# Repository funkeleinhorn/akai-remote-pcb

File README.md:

<!--
SPDX-FileCopyrightText: 2025 Funkeleinhorn <git@funkeleinhorn.com>
SPDX-License-Identifier: GPL-3.0-or-later
-->

# Keymatrix

A PCB which fits in the remote control port of AKAI GX 635s featuring an ESP32 to allow remote control.
This project is licensed as open hardware. See LICENSE.txt for details.

## Images

Here you can see how the PCB looks:

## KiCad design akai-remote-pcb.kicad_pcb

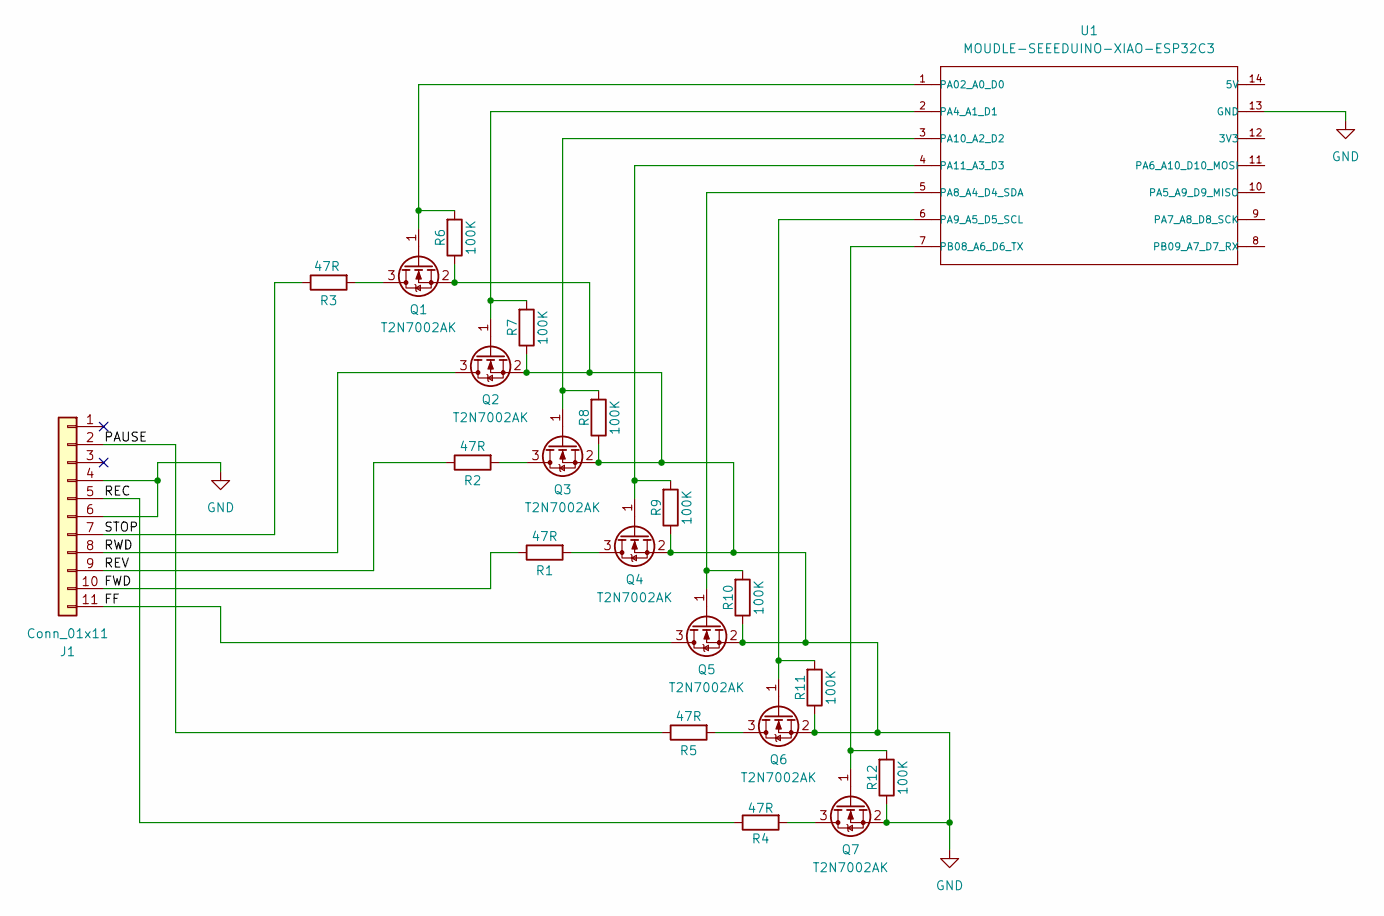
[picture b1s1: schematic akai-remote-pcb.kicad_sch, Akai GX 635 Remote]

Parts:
J1: Conn_01x11; AKAI_GX_635_REMOTE_CONTROL_PORT
Q1, Q2, Q3, Q4, Q5, Q6, Q7: T2N7002AK; SOT-23
R1, R2, R3, R4, R5: 47R; R_0603_1608Metric
R6, R7, R8, R9, R10, R11, R12: 100K; R_0603_1608Metric
U1: MOUDLE-SEEEDUINO-XIAO-ESP32C3; MOUDLE14P-SMD-2.54-21X17.8MM

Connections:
/FF: J1.11, Q5.3 (D)
/FWD: J1.10, R1.1
/PAUSE: J1.2, R5.1
/REC: J1.5, R4.1
/REV: J1.9, R2.1
/RWD: J1.8, Q2.3 (D)
/STOP: J1.7, R3.1
GND: J1.4, J1.6, Q1.2 (S), Q2.2 (S), Q3.2 (S), Q4.2 (S), Q5.2 (S), Q6.2 (S), Q7.2 (S), R6.1, R7.1, R8.1, R9.1, R10.1, R11.1, R12.1, U1.13 (GND)
unnamed: Q1.3 (D), R3.2
unnamed: Q1.1 (G), R6.2, U1.1 (PA02_A0_D0)
unnamed: Q2.1 (G), R7.2, U1.2 (PA4_A1_D1)
unnamed: Q3.3 (D), R2.2
unnamed: Q3.1 (G), R8.2, U1.3 (PA10_A2_D2)
unnamed: Q4.3 (D), R1.2
unnamed: Q4.1 (G), R9.2, U1.4 (PA11_A3_D3)
unnamed: Q5.1 (G), R10.2, U1.5 (PA8_A4_D4_SDA)
unnamed: Q6.3 (D), R5.2
unnamed: Q6.1 (G), R11.2, U1.6 (PA9_A5_D5_SCL)
unnamed: Q7.3 (D), R4.2
unnamed: Q7.1 (G), R12.2, U1.7 (PB08_A6_D6_TX)

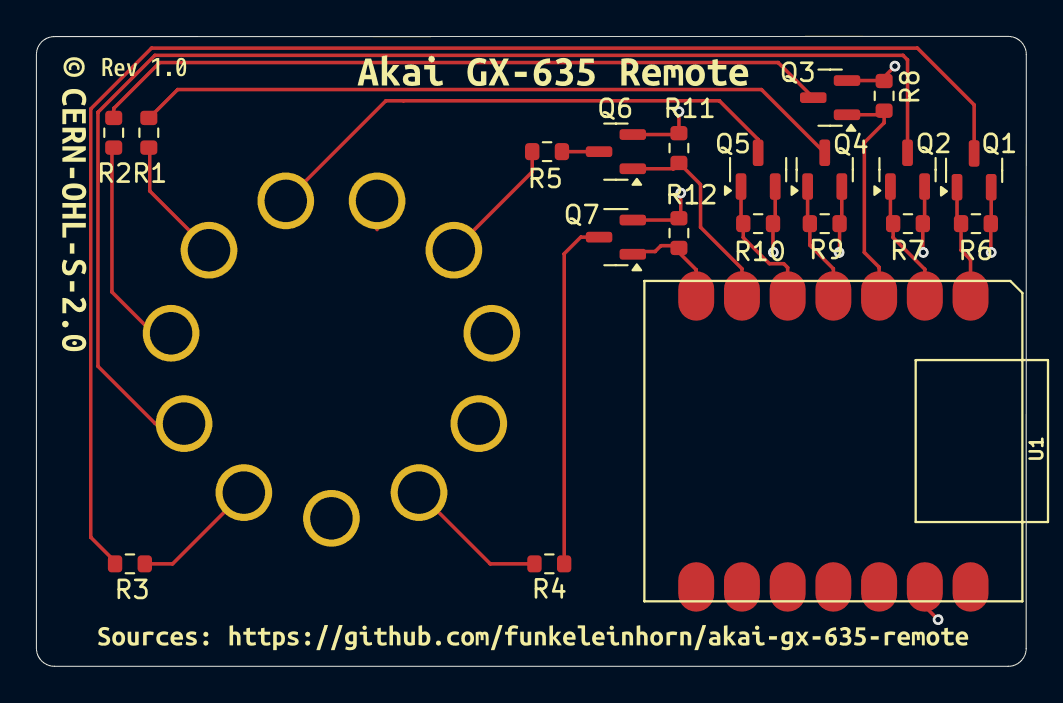
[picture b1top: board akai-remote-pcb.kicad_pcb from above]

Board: 2 copper layers, 55.0 x 35.0 mm, 26 parts (0 on the bottom side), 20 nets.

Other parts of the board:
kibuzzard-67B602E2: G***; kibuzzard-67B602E2
kibuzzard-67B602EE: G***; kibuzzard-67B602EE
kibuzzard-67B60253: G***; kibuzzard-67B60253
kibuzzard-67B60319: G***; kibuzzard-67B60319
kibuzzard-68D13955: G***; kibuzzard-68D13955

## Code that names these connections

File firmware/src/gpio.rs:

// SPDX-FileCopyrightText: 2025 Funkeleinhorn <git@funkeleinhorn.com>
//
// SPDX-License-Identifier: GPL-3.0-or-later

use core::{
    future::join,
    sync::atomic::{AtomicBool, Ordering},
};

use embassy_time::{Duration, Timer};
use esp_hal::gpio::Output;

pub static GPIO_PAUSE_STATE: AtomicBool = AtomicBool::new(false);
pub static GPIO_REC_STATE: AtomicBool = AtomicBool::new(false);
pub static GPIO_STOP_STATE: AtomicBool = AtomicBool::new(false);
pub static GPIO_RWD_STATE: AtomicBool = AtomicBool::new(false);
pub static GPIO_REV_STATE: AtomicBool = AtomicBool::new(false);
pub static GPIO_FWD_STATE: AtomicBool = AtomicBool::new(false);
pub static GPIO_FF_STATE: AtomicBool = AtomicBool::new(false);

async fn trigger_gpio(state: &AtomicBool, gpio: &mut Output<'static>) {
    if state.load(Ordering::Relaxed) {
        gpio.set_high();
        Timer::after(Duration::from_millis(1000)).await;
        gpio.set_low();
        state.store(false, Ordering::Relaxed);
    } else {
        gpio.set_low();
    }
}

#[embassy_executor::task]
pub async fn gpio_task(
    mut pause_gpio: Output<'static>,
    mut rec_gpio: Output<'static>,
    mut stop_gpio: Output<'static>,
    mut rwd_gpio: Output<'static>,
    mut rev_gpio: Output<'static>,
    mut fwd_gpio: Output<'static>,
    mut ff_gpio: Output<'static>,
) {
    loop {
        let pause_fut = trigger_gpio(&GPIO_PAUSE_STATE, &mut pause_gpio);
        let rec_fut = trigger_gpio(&GPIO_REC_STATE, &mut rec_gpio);
        let stop_fut = trigger_gpio(&GPIO_STOP_STATE, &mut stop_gpio);
        let rwd_fut = trigger_gpio(&GPIO_RWD_STATE, &mut rwd_gpio);
        let rev_fut = trigger_gpio(&GPIO_REV_STATE, &mut rev_gpio);
        let fwd_fut = trigger_gpio(&GPIO_FWD_STATE, &mut fwd_gpio);
        let ff_fut = trigger_gpio(&GPIO_FF_STATE, &mut ff_gpio);
        join!(pause_fut, rec_fut, stop_fut, rwd_fut, rev_fut, fwd_fut, ff_fut).await;
        Timer::after(Duration::from_millis(50)).await;
    }
}

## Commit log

2025-09-13 Fix MOSFET direction and add external pull-down resistors
    This commit fixes the direction of the MOSFETs and adds external
    pull-down resistors to their gates to prevent undefined behavior when
    the ESP is not powered.
2025-09-13 chore: update schematic PDF [skip ci]
2025-10-06 Fix remote connector pinout, rework routing for cleaner design
    This commit fixes the pinout of the Akai GX 635 remote connector
    which was wrong in older revisions. To allow for cleaner routing
    the wiring of remote connector pins to the MOSFETs was changed.
2025-10-06 Move KiCad PCB project to hardware folder
    This commit moves the PCB project into a hardware folder as a
    preparation to add the corresponding firmware to one monorepo.
2025-10-06 Rework licensing information to conform to REUSE Spec v3.3
    This commit reworks the licensing information of this project to
    conform to the REUSE Specification – Version 3.3
    See https://reuse.software/ for more information.
2025-10-06 Add folder with Rust firmware providing a REST API for remote control
    This commit adds a ./firmware folder containing a embassy.rs based
    Rust firmware providing a REST API to control the Akai with.
2025-10-06 Add Nix Flake to provide a reproducible dev-environment
    This commit adds a Nix Flake which provides a reproducible environment
    for development and flashing. It can be automatically loaded if direnv
    is present.
